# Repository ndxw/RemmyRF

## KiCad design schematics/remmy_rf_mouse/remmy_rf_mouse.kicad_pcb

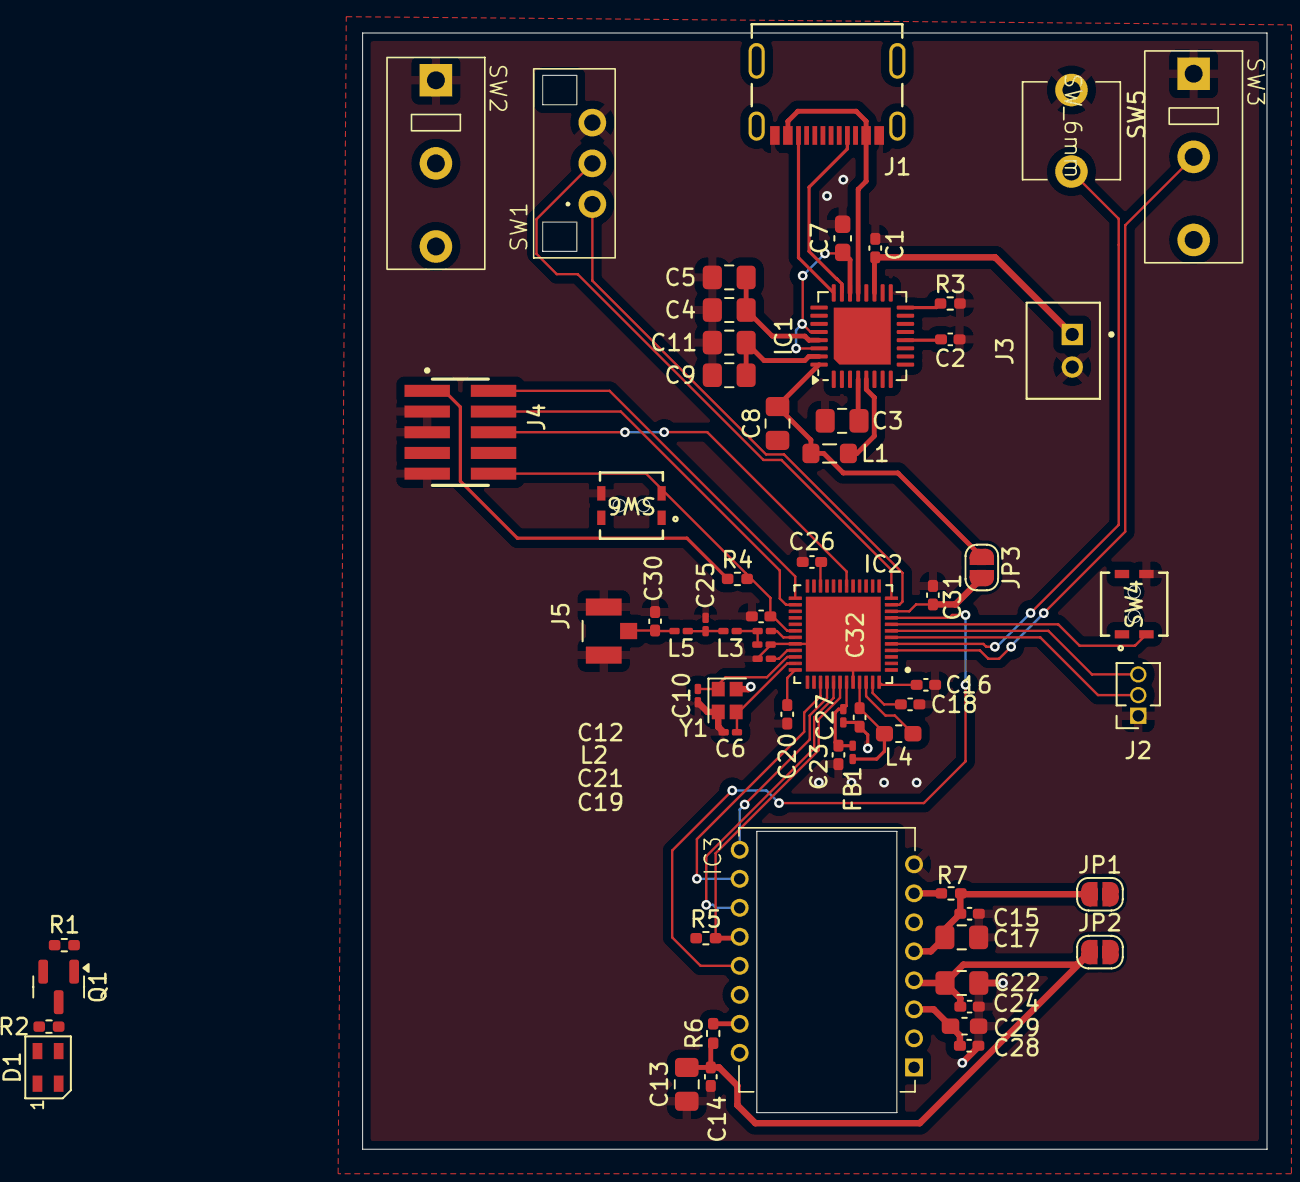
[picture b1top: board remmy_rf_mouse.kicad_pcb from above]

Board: 4 copper layers, 55.5 x 68.5 mm, 65 parts (0 on the bottom side), 51 nets.

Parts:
C1, C23, C32: 2.2u; C_0402_1005Metric_Pad0.74x0.62mm_HandSolder
C2, C18, C20, C26, C31: 100n; C_0402_1005Metric_Pad0.74x0.62mm_HandSolder
C3, C4, C5, C8, C9, C11, C13, C17, C22: 10u; C_0805_2012Metric_Pad1.18x1.45mm_HandSolder
C6, C10: C; C_0201_0603Metric_Pad0.64x0.40mm_HandSolder
C7: 1u; C_0603_1608Metric_Pad1.08x0.95mm_HandSolder
C12: 3.9p; C_0402_1005Metric_Pad0.74x0.62mm_HandSolder
C14, C15, C24, C28: 0.1u; C_0402_1005Metric_Pad0.74x0.62mm_HandSolder
C16: 10u; C_0402_1005Metric_Pad0.74x0.62mm_HandSolder
C19: 2.2n; C_0201_0603Metric_Pad0.64x0.40mm_HandSolder
C21: 1.5p; C_0201_0603Metric_Pad0.64x0.40mm_HandSolder
C25: 2p; C_0201_0603Metric_Pad0.64x0.40mm_HandSolder
C27: 10n; C_0201_0603Metric_Pad0.64x0.40mm_HandSolder
C29: 4.7u; C_0603_1608Metric_Pad1.08x0.95mm_HandSolder
C30: 0.3p; C_0402_1005Metric_Pad0.74x0.62mm_HandSolder
D1: SK6805; LED_SK6805_PLCC4_2.4x2.7mm_P1.3mm
FB1: 120; C_0201_0603Metric_Pad0.64x0.40mm_HandSolder
IC1: nPM1300-QEAA; QFN-32-1EP_5x5mm_P0.5mm_EP3.5x3.5mm
IC2: NRF54L15-QFAA-R
IC3: PMW3360DM-T2QU
J1: USB_C_Receptacle_USB2.0_14P; USB-C_16+8_dummy_SMD
J2: Conn_01x03_Pin; PinSocket_1x03_P1.27mm_Vertical
J3: PH2.0; CONN_JST_B2B-PH-K-S
J4: Conn_ARM_JTAG_SWD_10; CONN_ARM_JTAG_SWD_02x05_P1.27mm_SMD
J5: U.FL-R-SMT_10_; HIROSE_U.FL-R-SMT_10_
JP1, JP2, JP3: SolderJumper_2_Open; SolderJumper-2_P1.3mm_Open_RoundedPad1.0x1.5mm
L1: 2.2u; L_0805_2012Metric_Pad1.05x1.20mm_HandSolder
L2: 2.7n; L_0201_0603Metric_Pad0.64x0.40mm_HandSolder
L3, L5: 3.5n; L_0201_0603Metric_Pad0.64x0.40mm_HandSolder
L4: 4.7u; L_0603_1608Metric_Pad1.05x0.95mm_HandSolder
Q1: BSS138; SOT-23
R1, R2, R5, R7: 10k; R_0402_1005Metric_Pad0.72x0.64mm_HandSolder
R3: 300k; R_0402_1005Metric_Pad0.72x0.64mm_HandSolder
R4: 1k; R_0402_1005Metric_Pad0.72x0.64mm_HandSolder
R6: 39; R_0402_1005Metric_Pad0.72x0.64mm_HandSolder
SW1: RotaryEncoder; Encoder_TTC_Silver
SW2, SW3: Kailh GM 8.0; Kailh_GM_8.0
SW4, SW6: SW_Push; R-667_MIT
SW5: SW_Push; SW_PUSH_6mm
Y1: Crystal_GND24; Crystal_SMD_2016-4Pin_2.0x1.6mm

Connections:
+1.9V_LDO: C9.1, C11.1, IC1.31 (VOUTLDO2), JP2.2 (B)
+3.3V_BUCK: C31.1, IC2.10 (VDD), J4.1 (VTref), JP3.2 (B), Q1.1 (G), R1.1, R4.1
+3.3V_LDO: C4.1, C5.1, IC1.29 (VOUTLDO1), JP1.2 (B)
+5V_OVPROT: C7.1, D1.4 (VDD), IC1.22 (VBUSOUT), IC1.28 (VINLDO1), IC1.30 (VINLDO2), R2.1
ANTENNA: IC2.31 (ANT), L2.1
ARGB: Q1.2 (S), R1.2
DPI: IC2.8 (P1.07/ASI(1)/AIN3), SW4.2
ENC_A: IC2.11 (P2.00), SW1.A
ENC_B: IC2.12 (P2.01), SW1.B
GND: C1.2, C2.1, C3.2, C4.2, C5.2, C6.1, C7.2, C8.2, C9.2, C10.2, C11.2, C12.2, C13.1, C14.2, C15.2, C16.1, C17.2, C18.1, C19.2, C20.2, C21.2, C22.2, C23.2, C24.2, C25.2, C26.2, C27.2, C28.2, C29.2, C30.2, C31.2, C32.2, D1.2 (VSS), IC1.2 (PVSS1), IC1.6 (PVSS2), IC1.17 (VSET1), IC1.33 (AVSS), IC2.32 (VSS_PA), IC2.44 (VSS), IC2.49 (VSS__1), IC3.8 (GND), J1.A1 (GND), J1.B1 (GND), J2.1, J3.2, J4.3 (GND), J4.5 (GND), J4.9 (GNDDetect), J5.G1, J5.G2, R3.2, SW1.C, SW2.1 (COM), SW3.1 (COM), SW4.1, SW5.1, SW6.1, Y1.2, Y1.4
MOTION: IC2.40 (P1.12/ASI(3)/RADIO(3)/AIN5), IC3.9 (MOTION)
MOUSE1: IC2.3 (P1.02/NFC1), SW2.2 (NO)
MOUSE2: IC2.4 (P1.03/NFC2), SW3.2 (NO)
MOUSE4: IC2.6 (P1.05/ASI(0)/RADIO(6)/AIN1), J2.2
MOUSE5: IC2.7 (P1.06/ASO(1)/AIN2), J2.3
MWHEEL_BUTTON: IC2.5 (P1.04/ASO(0)/AIN0), SW5.2
unnamed: C21.1, L2.2, L3.1
unnamed: C25.1, L3.2, L5.1
unnamed: C30.1, J5.SIG, L5.2
unnamed: D1.3 (DIN), Q1.3 (D), R2.2
unnamed: IC1.23 (CC1), J1.A5 (CC1)
unnamed: IC1.24 (CC2), J1.B5 (CC2)
unnamed: C3.1, IC1.1 (VOUT1), IC1.4 (PVDD), IC1.20 (VSYS)
unnamed: IC1.5 (SW2), L1.1
unnamed: C1.1, IC1.19 (VBAT), J3.1
unnamed: IC1.21 (VBUS), J1.A4 (VBUS), J1.B4 (VBUS)
unnamed: C2.2, IC1.12 (VDDIO)
unnamed: C8.1, IC1.32 (VOUT2), JP3.1 (A), L1.2
unnamed: IC1.16 (VSET2), R3.1
unnamed: IC2.46 (DCC), L4.1
unnamed: C19.1, C23.1, C27.1, FB1.2, IC2.33 (DECRF), IC2.43 (DECA)
unnamed: C32.1, FB1.1, IC2.45 (DECD), L4.2
unnamed: C26.1, IC2.22 (VDD__1)
unnamed: C20.1, IC2.36 (VDD__2)
unnamed: C18.2, IC2.47 (VDD__3)
unnamed: C16.2, IC2.48 (VDD__4)
unnamed: IC3.15 (LED_P), R6.2
unnamed: IC3.7 (NRESET), R7.2
unnamed: C13.2, C14.1, C22.1, C24.1, IC3.4 (VDD), JP2.1 (A), R6.1
unnamed: C15.1, C17.1, IC3.5 (VDDIO), JP1.1 (A), R5.1, R7.1
unnamed: C28.1, C29.1, IC3.3 (VDDPIX)
SPI_CLK: IC2.39 (P1.11/ASO(3)/RADIO(2)/AIN4), IC3.10 (SCLK)
SPI_MISO: IC2.42 (P1.14/RADIO(5)/AIN7), IC3.12 (MISO), R5.2
SPI_MOSI: IC2.41 (P1.13/RADIO(4)/AIN6), IC3.11 (MOSI)
SPI_NCS: IC2.9 (P1.08/CLK16M/EXTREF), IC3.13 (NCS)
SWDCLK: IC2.26 (SWDCLK), J4.4 (SWCLK/TCK)
SWDIO: IC2.25 (SWDIO), J4.2 (SWDIO/TMS)
SWO: IC2.18 (P2.07/TRACEDATA(0)/SWO), J4.6 (SWO/TDO)
XC1: C10.1, IC2.34 (XC1), Y1.1
XC2: C6.2, IC2.35 (XC2), Y1.3
nRESET: C12.1, IC2.30 (~RESET), J4.10 (~RESET), R4.2, SW6.2

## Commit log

2025-07-06 init commit
2025-09-21 added power management
2025-09-23 fixed most footprints, just matching network left
